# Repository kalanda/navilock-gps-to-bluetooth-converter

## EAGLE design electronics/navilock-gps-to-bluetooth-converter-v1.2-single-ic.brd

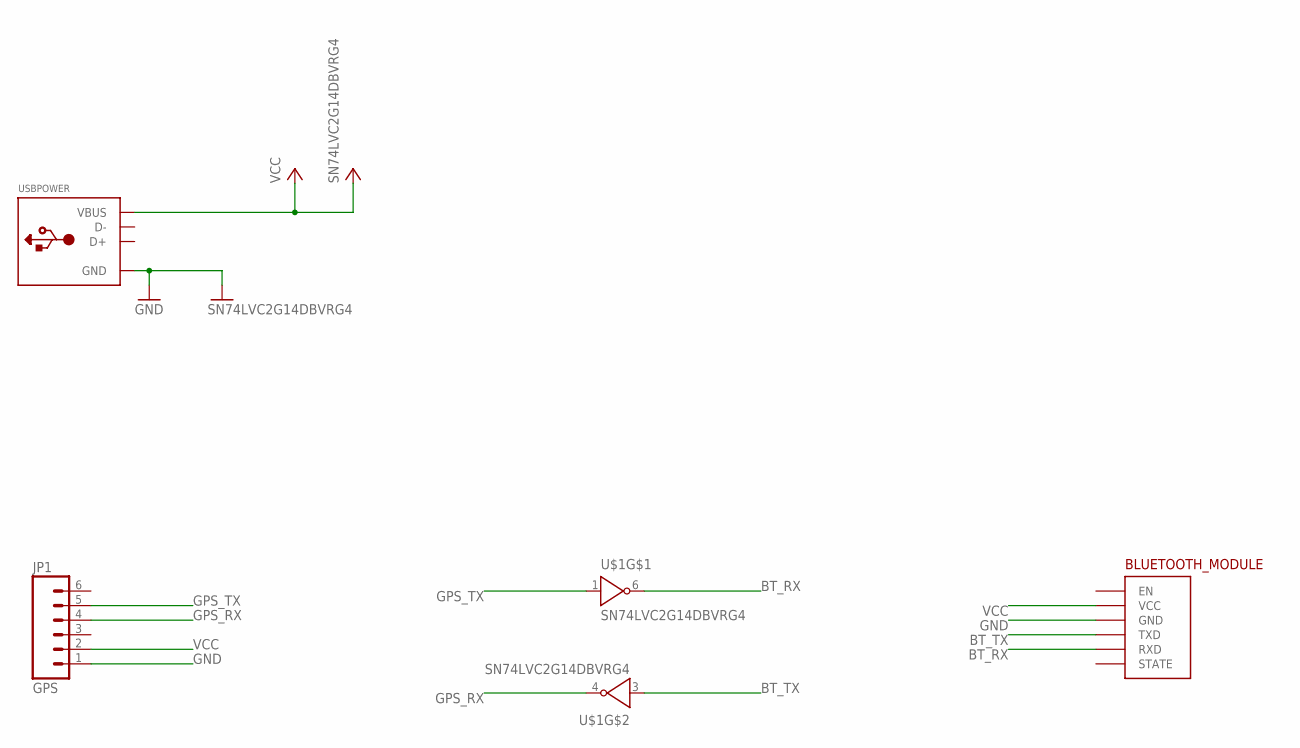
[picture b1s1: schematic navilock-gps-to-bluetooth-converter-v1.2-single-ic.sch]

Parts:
BLUETOOTH_MODULE: JY-MCU-BLUETOOTHHORIZONTAL; JY-MCU-BLUETOOTH-HORIZONTAL
JP1: GPS; MINI-DIN6-WITH-LAT-HOLES
U$1: SN74LVC2G14DBVRG4; SOT23-6
USBPOWER: USB_TYPEA; USB_A-SMT

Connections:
BT_RX: BLUETOOTH_MODULE.RXD, U$1.6 (O)
BT_TX: BLUETOOTH_MODULE.TXD, U$1.3 (I)
GND: BLUETOOTH_MODULE.GND, JP1.1, U$1.2 (GND), USBPOWER.GND
GPS_RX: JP1.4, U$1.4 (O)
GPS_TX: JP1.5, U$1.1 (I)
VCC: BLUETOOTH_MODULE.VCC, JP1.2, U$1.5 (VCC), USBPOWER.VBUS

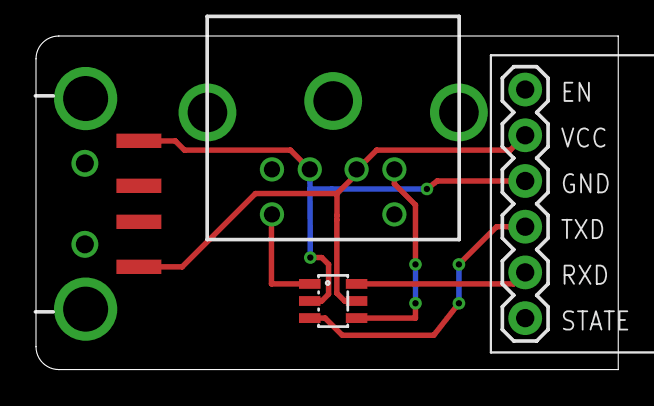
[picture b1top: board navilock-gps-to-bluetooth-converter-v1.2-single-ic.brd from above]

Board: 2 copper layers, 32.3 x 18.5 mm, 4 parts (0 on the bottom side), 6 nets.

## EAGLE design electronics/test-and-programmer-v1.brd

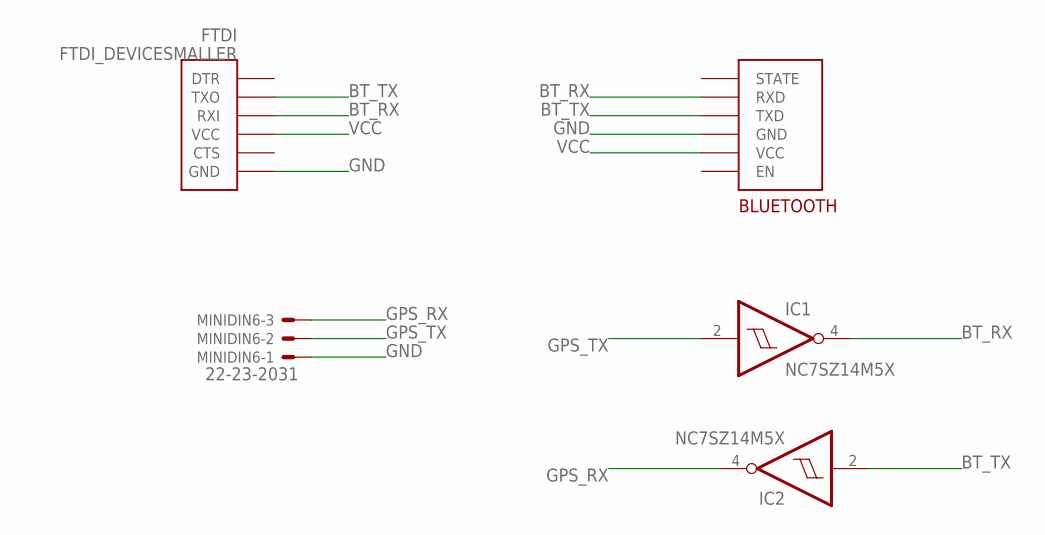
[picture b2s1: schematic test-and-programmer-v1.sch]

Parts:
BLUETOOTH: JY-MCU-BLUETOOTHHORIZONTAL; JY-MCU-BLUETOOTH-HORIZONTAL
FTDI: FTDI_DEVICESMALLER; FTDI_DEVICE_SIDE_SMALLER
IC1, IC2: NC7SZ14M5X; SOT23-5
MINIDIN6: 22-23-2031

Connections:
BT_RX: BLUETOOTH.RXD, FTDI.P$3 (RXI), IC1.4 (O)
BT_TX: BLUETOOTH.TXD, FTDI.P$2 (TXO), IC2.2 (I)
GND: BLUETOOTH.GND, FTDI.P$6 (GND), IC1.3 (GND), IC2.3 (GND), MINIDIN6.1
GPS_RX: IC2.4 (O), MINIDIN6.3
GPS_TX: IC1.2 (I), MINIDIN6.2
VCC: BLUETOOTH.VCC, FTDI.P$4 (VCC), IC1.5 (VCC), IC2.5 (VCC)

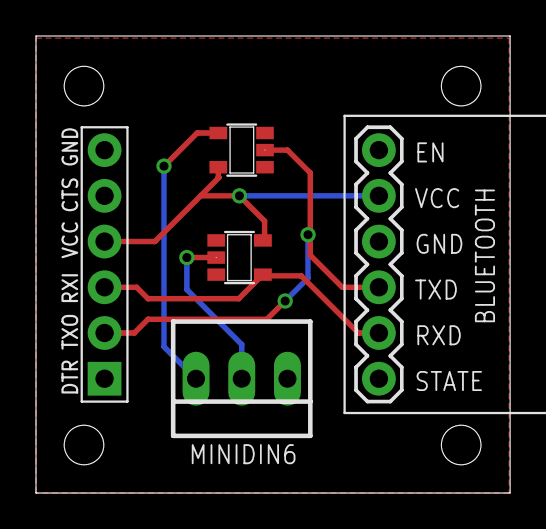
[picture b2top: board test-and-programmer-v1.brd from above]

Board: 2 copper layers, 26.3 x 25.4 mm, 5 parts (0 on the bottom side), 6 nets.

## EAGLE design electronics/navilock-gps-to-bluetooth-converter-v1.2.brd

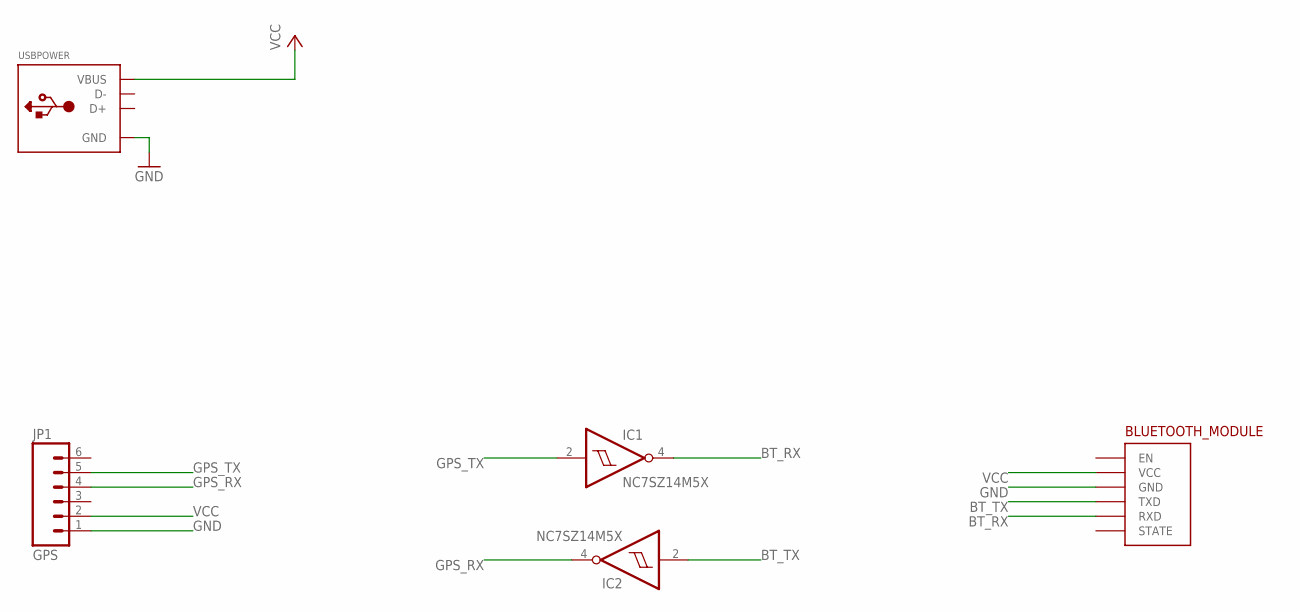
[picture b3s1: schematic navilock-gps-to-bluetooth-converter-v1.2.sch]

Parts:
BLUETOOTH_MODULE: JY-MCU-BLUETOOTHHORIZONTAL; JY-MCU-BLUETOOTH-HORIZONTAL
IC1, IC2: NC7SZ14M5X; SOT23-5
JP1: GPS; MINI-DIN6-WITH-LAT-HOLES
USBPOWER: USB_TYPEA; USB_A-SMT

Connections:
BT_RX: BLUETOOTH_MODULE.RXD, IC1.4 (O)
BT_TX: BLUETOOTH_MODULE.TXD, IC2.2 (I)
GND: BLUETOOTH_MODULE.GND, IC1.3 (GND), IC2.3 (GND), JP1.1, USBPOWER.GND
GPS_RX: IC2.4 (O), JP1.4
GPS_TX: IC1.2 (I), JP1.5
VCC: BLUETOOTH_MODULE.VCC, IC1.5 (VCC), IC2.5 (VCC), JP1.2, USBPOWER.VBUS

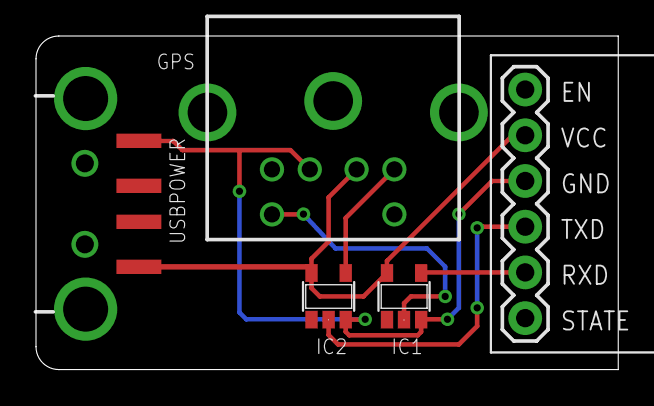
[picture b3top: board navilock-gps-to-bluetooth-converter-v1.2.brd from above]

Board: 2 copper layers, 32.3 x 18.5 mm, 5 parts (0 on the bottom side), 6 nets.

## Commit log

2017-08-10 Added shell script for loop setup and test
2017-12-31 Enhanced loop.sh
2017-12-31 Updated case file
2017-12-31 Added version of board with single IC with dual inverter
2018-05-21 Check for keypress in the loop script at the beginning

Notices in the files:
parts and their libraries:
microbuilder: This work is placed in the public domain, and may be freely used for commercial and non-commercial work with the following conditions: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
